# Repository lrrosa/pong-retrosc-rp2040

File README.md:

# RetroSC Pong — Raspberry Pi Pico (RP2040)

Pong para 1 ou 2 jogadores em um Raspberry Pi Pico, com saída de **vídeo
composto** (NTSC 1-bit gerado por PIO) e **áudio PWM**. Foi feito para uma
máquina arcade do evento [**RetroSC**](https://retrosc.org/).

## Recursos

- Vídeo composto NTSC 256×192, 1-bit, ~60 Hz, gerado inteiramente em PIO + DMA
  (CPU livre para o jogo).
- 2 raquetes controladas por **potenciômetros 10 kΩ** (ADC do Pico).
- **Dois modos**, escolhidos no menu do attract: **arcade** (1 jogador contra a
  CPU) e **versus** (2 jogadores). Os dois jogam as mesmas fases.
- **10 fases** em sequência, em ordem crescente de dificuldade, cada uma até
  9 pontos, e cada ponto soma no **total geral**:
  1. **PONG CLASSICO** — o pong de sempre;
  2. **TRIPLO** — a raquete vira 3 pedaços de 8 px com vãos entre eles;
  3. **NAVE** — uma nave sobe e desce no meio da quadra atirando: **a bola
     rebate nela** e o tiro que pega uma raquete deixa ela pela metade por 5 s;
  4. **BARREIRA I** — 2 muros de tijolos quebráveis no meio da tela;
  5. **PINBALL** — sete obstáculos fixos no meio da quadra: um losango com um
     poste solto acima e outro abaixo;
  6. **BARREIRA II** — 3 muros, agora espaçados entre si;
  7. **COLUNA** — cinco dos mesmos obstáculos, empilhados no meio e subindo e
     descendo juntos;
  8. **MURALHA** — uma parede de tijolos atrás de cada raquete: só marca ponto
     quem enfia a bola num dos vãos (a parede se refaz a cada ponto);
  9. **REBOUND** — vôlei: as raquetes deitam no chão e andam na horizontal
     dentro da própria meia-quadra, a bola tem gravidade e o ponto sai quando
     ela toca o chão do lado adversário;
  10. **BARREIRA III** — 4 muros (2 por jogador), já divididos em blocos de
      5-4-2-4-5 fileiras com um corredor vazio entre eles: a mais dura, por
      isso fecha o jogo.

  Nas três barreiras o estrago fica até o fim da fase: quando abre um vão de
  ponta a ponta, aquela fase volta a ser um pong normal.
- **Mascote-bônus**: em algumas fases (as que têm a quadra mais limpa) o
  mascote da RetroSC cruza a tela na diagonal — às vezes de cima para baixo,
  às vezes de baixo para cima — com a palavra **BONUS** piscando ao lado. Ele
  passa **no máximo duas vezes por fase**, e acertá-lo com a bola vale
  **3 pontos no total geral** de quem rebateu por último; o placar da fase não
  muda, e o total fica piscando um instante para o jogador perceber.
- **Pausa**: apertar o SELETOR durante a partida abre *CONTINUAR* / *SAIR DO
  JOGO*. A escolha anda pelo **movimento** do pot (não pela posição dele), então
  o menu sempre abre em *CONTINUAR*; o SELETOR confirma e sair volta ao attract.
  Passados **30 s**, a opção destacada vale sozinha — a tela não fica parada
  para sempre numa máquina de evento.
  Ao voltar ao jogo, a raquete de quem mexeu no pot durante a pausa fica
  **piscando e parada** até o pot voltar ao lugar em que estava — pausar não
  serve para reposicionar a raquete e salvar uma bola perdida.
- **Attract screen** com logo da RetroSC + demo automático (AI vs AI),
  revezando com a tabela de recordes a cada 20 s, e um **menu de modo** que só
  aparece depois de apertar o botão **SELETOR**.
- **High scores persistentes** na flash do RP2040 com **iniciais de 3 letras**
  estilo arcade — o pot escolhe cada letra e o botão SELETOR confirma. O que
  entra no ranking é o **total acumulado** (no arcade, sempre o do humano —
  ou seja, quanto ele fez até a fase em que parou).
- Áudio com os sons clássicos do Pong (raquete, parede, ponto) mais tijolo
  quebrado e beeps do menu, em PWM filtrado.
- Botão **SELETOR**: abre o menu, escolhe o modo e confirma as iniciais.

## Estrutura do repositório

```
pong-rp2040/
├── CMakeLists.txt
├── pico_sdk_import.cmake
├── README.md
├── LICENSE
├── docs/
│   ├── schematic.md     <-- esquemático por blocos (diagramas SVG)
│   ├── pinout.md        <-- pinagem dos 3 módulos RP2040 suportados
│   ├── bom.md           <-- lista de materiais (por referência: R1, C2, J4…)
│   ├── pecas-do-gabinete.md  <-- pots, knobs e itens da caixa: qual comprar
│   └── images/          <-- diagramas, renders da placa, capturas
├── kicad/               <-- PCB: 2 variantes, gerbers prontos p/ fábrica
│   ├── README.md        <-- pipeline (esquemático -> placa -> gerbers)
│   ├── retrosc-pong*.kicad_{sch,pcb,pro}
│   ├── retrosc-pong.pretty/   <-- footprints próprios (RCA, PAM8403)
│   └── gerbers*/ + *-gerbers.zip
├── src/
│   ├── main.c
│   ├── config.h         <-- constantes do projeto (pinos, dimensões, etc.)
│   ├── ntsc.{c,h,pio}   <-- driver de vídeo composto
│   ├── gfx.{c,h}        <-- desenho no framebuffer
│   ├── font.{c,h}       <-- fonte 5x7
│   ├── input.{c,h}      <-- ADC dos pots + botão
│   ├── audio.{c,h}      <-- PWM de áudio
│   ├── highscores.{c,h} <-- persistência na flash
│   ├── game.{c,h}       <-- máquina de estados, modos e física
│   ├── phases.{c,h}     <-- as 4 fases (raquetes especiais, tijolos)
│   └── assets.{c,h}     <-- bitmaps embutidos
└── tools/
    ├── png_to_c.py      <-- conversor PNG → C array
    ├── sim.py           <-- simulador do jogo (pygame)
    ├── crt_preview.py   <-- efeito de tubo nas capturas
    ├── gen_kicad_sch.py <-- gera o esquemático  (--yd p/ a variante)
    ├── gen_kicad_fp.py  <-- gera os footprints próprios
    ├── gen_kicad_pcb.py <-- gera a placa (placement, zonas, silk, logo)
    ├── make_decoy.py    <-- placa-isca p/ o Freerouting + DSN
    ├── import_ses.py    <-- traz o roteamento de volta
    └── dsn_tweak.py     <-- ajusta larguras/isolamento no DSN
```

## Hardware

Veja os arquivos em [docs/](docs/) para detalhes:

- [docs/schematic.md](docs/schematic.md) — esquemático completo
- [docs/pinout.md](docs/pinout.md) — pinagem dos **3 módulos RP2040
  suportados** (Pico oficial, YD-RP2040 de 3 botões e "roxa" de 1 botão) e
  qual variante de PCB usar com cada um
- [docs/bom.md](docs/bom.md) — lista de materiais e custo
- [docs/pecas-do-gabinete.md](docs/pecas-do-gabinete.md) — potenciômetros,
  manoplas e peças da caixa: **qual modelo comprar** e por quê
- [kicad/README.md](kicad/README.md) — as **duas variantes de PCB** prontas
  para fabricar (gerbers zipados)

Resumo do hardware:

| Bloco | GPIO | Componentes (referências do BOM) |
| ----- | ---- | -------------------------------- |
| Vídeo composto | GP16 (sync), GP17 (video) | R1 470 Ω + R2 270 Ω → jack J1 |
| Áudio | GP18 (PWM) | filtro R3 + C1, acoplamento C2, divisor R4/R5, entradas R6/R7 → amp U2 → jacks J8/J9 |
| Botão SELETOR | GP22 | SW1 (para GND) via header J7 |
| Potenciômetro P1 | GP26 (ADC0) | RV1 10 kΩ linear + C3 → header J5 |
| Potenciômetro P2 | GP27 (ADC1) | RV2 10 kΩ linear + C4 → header J6 |

Os GPIOs acima são os mesmos nos três módulos suportados; o que muda entre
eles é **em qual furo** cada GPIO aparece (ver [pinout.md](docs/pinout.md)).

## Como compilar

### 1. Instalar o Pico SDK

**Recomendado (Windows):** baixe o [Raspberry Pi Pico Windows Installer](https://github.com/raspberrypi/pico-setup-windows/releases),
que instala toolchain (ARM GCC), CMake, Ninja, Python e o Pico SDK de uma
vez.

**Manual (qualquer SO):**

```bash
git clone --depth 1 https://github.com/raspberrypi/pico-sdk.git
cd pico-sdk
git submodule update --init
export PICO_SDK_PATH=$(pwd)
```

Instale também:

- ARM GCC (`gcc-arm-none-eabi`)
- CMake ≥ 3.13
- Ninja ou Make

### 2. Build

```bash
git clone https://github.com/lrrosa/retrosc-pong.git
cd retrosc-pong
mkdir build && cd build
cmake -G "Ninja" ..   # ou simplesmente: cmake ..
ninja                 # ou: make -j
```

Resultado: `build/pong-rp2040.uf2`.

### 3. Gravar no Pico

1. Segure o botão **BOOTSEL** do Pico enquanto conecta o USB.
2. O Pico aparece como pendrive (`RPI-RP2`).
3. Arraste `pong-rp2040.uf2` para dentro do pendrive.
4. O Pico reinicia automaticamente rodando o jogo.

## Simulador (Python, sem hardware)

Para iterar em layouts e gameplay sem flashear o Pico, há um simulador que
roda a mesma lógica em Python e carrega os MESMOS bitmaps/fonte do código C:

```bash
pip install pygame
python tools/sim.py
```

Janela 768×576 (framebuffer 256×192 × 3). Controles:

- **Mouse Y na metade esquerda** → pot P1
- **Mouse Y na metade direita** → pot P2
- **Espaço** → botão SELETOR
- **N** → pula para a próxima fase (atalho de debug)
- `--fase N` na linha de comando → começa direto na fase N (0 a 9)
- **R** → zera high scores (só em RAM, não toca a flash do Pico)
- **Q** ou **ESC** → sair

Para regerar as capturas de tela usadas aqui (roda sem abrir janela):

```bash
python tools/sim.py --shots docs/images
python tools/crt_preview.py --all
```

Pré-visualizações com efeito CRT (como deve ficar numa TV de tubo —
scanlines, glow de fósforo, vignette e curvatura):

| Attract | Menu (só após o SELETOR) | Pausa |
| :---: | :---: | :---: |
|  |  |  |

As dez fases:

| 1 · pong clássico (com o mascote-bônus) | 2 · triplo | 3 · nave |
| :---: | :---: | :---: |
|  |  |  |

| 4 · barreira I | 5 · pinball | 6 · barreira II |
| :---: | :---: | :---: |
|  |  |  |

| 7 · coluna | 8 · muralha | 9 · rebound (vôlei) |
| :---: | :---: | :---: |
|  |  |  |

| 10 · barreira III | Fim de fase | Início de fase |
| :---: | :---: | :---: |
|  |  |  |

| Game Over | Enter Initials | High Scores |
| :---: | :---: | :---: |
|  |  |  |

Renderizações "raw" (sem CRT, só o framebuffer escalado) ficam em
`docs/images/sim_*.png`.

> **Limitação:** o simulador não reproduz a fidelidade do sinal NTSC nem
> o timing exato do PIO/DMA. Use para validar UX e visual; o teste final
> do vídeo só com a TV real.

### CRT preview

Para aplicar o efeito CRT (scanlines + bloom + fósforo + vignette +
curvatura) em qualquer PNG do framebuffer:

```bash
pip install pillow numpy
python tools/crt_preview.py docs/images/sim_attract.png        # gera crt_sim_attract.png
python tools/crt_preview.py --all                              # regenera todos os crt_*.png
```

Os parâmetros (intensidade do bloom, dos scanlines, cor do fósforo) estão
no topo de `crt_effect()` em [tools/crt_preview.py](tools/crt_preview.py)
e são bons pontos de partida; mexa neles pra ajustar pra TV verde, âmbar,
ou ajustar o "estado" do tubo.

## Simulador Wokwi (TV de verdade no navegador)

Diferente do simulador Python (que reproduz a lógica do jogo), o **Wokwi roda
o firmware compilado de verdade** no RP2040 emulado e mostra a saída de vídeo
composto numa **TV virtual** (`wokwi-tv`), com potenciômetros, botão e buzzer.

O `wokwi-tv` não usa DAC resistivo: ele lê os 2 pinos digitais direto e segue
os pulsos de sync (funciona com NTSC e PAL). Os arquivos já estão no repo:

- [`diagram.json`](diagram.json) — fiação: `GP16→SYNC`, `GP17→IN`, 2
  potenciômetros em `GP26`/`GP27`, botão SELETOR em `GP22`, buzzer em `GP18`.
- [`wokwi.toml`](wokwi.toml) — aponta para `build/pong-rp2040.uf2`/`.elf`.

Como rodar (extensão do VS Code, mais confiável que o site):

```bash
# 1. Compile o firmware
mkdir build && cd build && cmake -G Ninja .. && ninja && cd ..
# 2. No VS Code: instale a extensão "Wokwi for VS Code" e faça login (grátis)
# 3. Abra diagram.json e rode o comando "Wokwi: Start Simulator"
```

Controles no Wokwi: gire os **potenciômetros** (mouse) para mover as raquetes;
**botão verde** = SELETOR.

> **Importante:** abra a pasta `pong-rp2040` como raiz do workspace do VS Code
> (o `wokwi.toml` precisa estar na raiz). Se clicar em "play" e nada acontecer,
> rode antes `Ctrl+Shift+P` → "Wokwi: Request a New License" (token gratuito).

> **Velocidade:** o Wokwi roda a ~30% do tempo real — é normal. Emular o vídeo
> composto ciclo-a-ciclo no navegador é pesado. O **hardware real roda a 60 fps**
> (PIO + DMA fazem o vídeo, a CPU fica livre).

> **Se o Wokwi não abre no seu navegador:** ele exige WebAssembly + isolamento
> cross-origin (`SharedArrayBuffer`); extensões ou políticas às vezes bloqueiam.
> Use a **extensão do VS Code** (roda local) ou teste numa aba anônima. Se nem
> os projetos públicos do Wokwi rodam aí, conserte isso antes — não é do nosso
> projeto.

> **Centralização Wokwi × TV real:** a "janela visível" do `wokwi-tv` é
> deslocada para cima, então `LINES_TOP_BLANK` (em `src/config.h`) está em **55**
> para centralizar no simulador. Numa **TV CRT real** o centro padrão fica em
> **~30–35** — reduza esse valor (ou use o controle de V-Position/V-Hold da TV).
> A posição horizontal sai do "back porch" em `src/ntsc.pio`.

## Como jogar

- **Liga**: conecte alimentação (USB ou fonte 5 V). Sem ninguém jogando, a
  tela reveza entre o attract e a tabela de recordes.
- **Sair do attract**: aperte o **SELETOR** (vale também na tela de recordes).
  Só então o menu aparece — no attract ele fica escondido, para a tela seguir
  sendo a vitrine do jogo.
- **Escolher o modo**: com o menu aberto, **gire qualquer um dos dois pots**
  para trocar entre *MODO ARCADE* (1 jogador × CPU) e *MODO VERSUS*
  (2 jogadores) e aperte o **SELETOR** para confirmar. Sem toque nenhum por
  15 s, volta ao attract.
- **Jogar**: rode os potenciômetros para mover as raquetes (esquerda = P1,
  direita = P2 ou CPU). São **10 fases em sequência**, cada uma até **9
  pontos**, e todo ponto também soma no **total geral**. Cada fase começa com
  a bola indo para o lado de quem perdeu a fase anterior.
- **Como a partida acaba**:
  - No **modo arcade** ela termina assim que a CPU fecha uma fase — enquanto
    o jogador vencer, ele avança para a próxima. O placar dele é o total do
    que fez até ali, e a tela final mostra até que fase chegou.
  - No **modo versus** jogam-se as 10 fases e ganha quem tiver o maior total —
    mas a partida encerra antes se um dos dois **não alcançar mais o outro nem
    ganhando tudo o que falta**. A conta usa os pontos ainda em disputa (9 por
    fase restante, mais 6 nas fases que têm o bônus); se a diferença for
    exatamente igual a isso a partida continua, porque ainda dá empate. A tela
    de fim de fase avisa com *VANTAGEM DECISIVA*.
- **Ritmo**: a contagem 3-2-1 aparece só no primeiro ponto de cada fase; entre
  os pontos seguintes é só um "GO" rápido. Apertar o SELETOR pula as telas de
  início e de fim de fase — e, **durante a partida**, abre a pausa.
- **Iniciais**: se o total entrar no top 5, o jogador insere 3 letras estilo
  arcade — girar o pot rola pelo alfabeto A–Z, apertar o SELETOR confirma a
  letra atual e passa para a próxima. A tela tem **30 s**: no fim da contagem
  vale o que já estiver digitado. No modo arcade quem entra no ranking é
  sempre o humano (P1), tenha vencido ou não.
- **High scores**: depois das iniciais (ou direto, se não entrou no top),
  a tabela aparece por 10 s antes de voltar ao attract.

## Customização

Tudo importante está em [`src/config.h`](src/config.h):

- `PHASE_WIN_SCORE` — pontos para vencer **uma fase** (padrão 9). É o botão
  de volume da duração da partida. Medido no simulador: um jogador que vence
  as 10 fases leva ~18 min no arcade (quem perde na terceira sai em ~5 min), e
  uma partida versus equilibrada, que vai até a décima fase, passa de 30 min —
  quando um dos dois abre vantagem decisiva ela acaba antes. Para uma fila de
  evento, **5 pontos por fase** corta isso quase pela metade sem mudar mais
  nada.
- `AI_PADDLE_SPEED`, `AI_ERROR_PX` — dificuldade da CPU no modo arcade
  (velocidade em px/frame e erro de mira sorteado a cada rebatida).
- `BALL_SPEED_*` — física da bola
- `PADDLE_W`, `PADDLE_H`, `BALL_SIZE` — visual
- `BRICK_W`, `BRICK_H`, `TRIPLE_SEG_H`, `TRIPLE_GAP` — geometria das fases
- `BONUS_*` — o mascote-bônus: velocidade, inclinação, faixa horizontal, o
  intervalo sorteado entre passagens (`BONUS_WAIT_MIN/RANGE`), quantas vezes
  ele passa por fase (`BONUS_PASSES_MAX`) e quanto vale (`BONUS_POINTS`)
- `NAVE_*`, `SHOT_*`, `SHRINK_FRAMES` — a nave da fase 3, seus tiros e quanto
  tempo a raquete atingida fica pela metade
- `INITIALS_TIMEOUT_S`, `PAUSE_TIMEOUT_S` — os 30 s que cada tela de espera
  aguarda antes de decidir sozinha
- `BUMPER_*`, `COL_*`, `BUMPER_SPIN_SHIFT` — os obstáculos do pinball e da
  coluna móvel, e o quanto cada rebote neles gira a bola (o que impede que ela
  entre em vaivém eterno entre dois postes)
- `PAUSE_POT_STEP`, `PADDLE_TAKEOVER_TOL` — quanto girar o pot para trocar o
  item da pausa e a folga para a raquete voltar a obedecer depois dela
- `GRAVITY_Q`, `VOLLEY_*`, `NET_TOP` — a física do Rebound (vôlei)
- `MENU_TIMEOUT_S` — tempo até o menu desistir e voltar ao attract
- Pinos GPIO

As fases em si estão em [`src/phases.c`](src/phases.c): o enum `phase_id_t`,
as tabelas de nome/dica e as funções `build_*()`. Uma fase pode mexer em
quatro coisas — o formato/orientação da raquete, os tijolos e sólidos da
quadra, o ponto de saque e as *flags* (`PF_GRAVITY`, `PF_FLOOR_SCORES`,
`PF_SIDE_WALLS`, `PF_PADDLE_HORIZ`, `PF_NO_CENTER_LINE`, `PF_TEM_BONUS`) que
dizem ao `game.c` como tratar as bordas e a física e se o mascote-bônus
aparece ali. Para acrescentar uma fase basta um
item no enum, um nome/dica nas tabelas e o que ela tem de especial — o resto
do jogo (pontuação, menu, telas) não muda.

Ideias ainda na fila estão anotadas no topo de `phases.c`.

Para trocar o logo do attract:

```bash
python tools/png_to_c.py docs/images/seu_logo.png retrosc_logo 0 0 threshold > tools/_logo.inc
# Substituir o array correspondente em src/assets.c
```

Modo `threshold` (corte fixo em 128) é melhor para arte com contornos
definidos (logos, ícones). Modo `dither` (Floyd-Steinberg) é melhor para
fotos com gradientes — mas em 60 Hz num CRT, o padrão de dithering pode
ficar tremido. Para o evento, prefira `threshold`.

Veja `docs/images/preview_logo_1bit.png` para saber como ficou a versão
1-bit.

## Limitações conhecidas

- **NTSC monocromático**: sem cor. Em TVs PAL-M brasileiras, a maioria
  aceita o sinal sem problema (mostra em preto e branco). Se sua TV não
  aceita, talvez precise de uma TV CRT com entrada AV "real" ou um
  conversor.
- **Timing do PIO** está calculado para `clk_sys = 125 MHz`. Se você
  alterar o clock, ajuste `clkdiv` em `src/ntsc.c` proporcionalmente.
- **Serigrafia da PCB**: as placas da v1 têm o botão serigrafado como
  **START** (a net no KiCad também se chama `START`). O firmware, os diagramas
  e as telas já o chamam de **SELETOR** — é o mesmo botão no GP22.
- **Tabela de high scores zera ao atualizar**: o formato ganhou o campo de
  modo (`HISCORE_VERSION 3`), então a tabela gravada por firmwares antigos é
  descartada na primeira execução.

## Créditos e referências

- A abordagem de gerar NTSC com duas PIOs (sync + dados) + DMA é inspirada
  no trabalho de [@brucland](https://github.com/brucland/RP2040/tree/main/PIO/NTSC_1_bit).
  Este projeto é uma implementação independente (não copia o código), mas a
  análise daquele repositório foi essencial para definir o timing.
- Pong original: Allan Alcorn, Atari (1972).
- Logo da RetroSC: cortesia do evento [RetroSC](https://retrosc.org/).

## Licença

Projeto com **licença dupla** (ver [`NOTICE`](NOTICE) para o detalhamento por
arquivo):

- **Software** (firmware em `src/`, ferramentas em `tools/`, build) —
  **[GPL-3.0-or-later](LICENSE)** (`SPDX-License-Identifier: GPL-3.0-or-later`).
- **Hardware** (esquemáticos: `kicad/`, `docs/schematic.md`, `docs/bom.md`,
  `docs/pinout.md`, diagramas SVG) — **[CERN-OHL-S-2.0](LICENSE-HARDWARE.txt)**
  (`SPDX-License-Identifier: CERN-OHL-S-2.0`), a variante *Strongly Reciprocal*
  da CERN Open Hardware Licence.

As duas são **recíprocas** (copyleft): trabalhos derivados devem manter a mesma
licença e disponibilizar as fontes correspondentes (código no caso do software,
arquivos de projeto no caso do hardware).

As **marcas e arte do evento RetroSC** (logo) permanecem propriedade do evento e
**não** estão cobertas por essas licenças — ver [`NOTICE`](NOTICE).

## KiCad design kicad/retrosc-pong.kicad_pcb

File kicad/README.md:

# PCB — RetroSC Pong

Placa de 2 camadas com plano de terra, gerada por scripts (reprodutível) e
roteada com o Freerouting. Hardware sob **CERN-OHL-S-2.0** (ver
[`../LICENSE-HARDWARE.txt`](../LICENSE-HARDWARE.txt)).

| Montada | Sem componentes (serigrafia à mostra) |
| :---: | :---: |
|  |  |

**80 × 66 mm**, imagens da variante oficial (a YD é idêntica por fora; muda só
o roteamento). O logo RetroSC fica **embaixo do Pico** — por isso aparece na
serigrafia e não no render 3D. Layout detalhado em [Estado](#estado).

> O **Pico é o único componente com modelo 3D** (os footprints próprios do RCA
> e do PAM8403 não têm) — e é justamente ele que cobre o logo. Por isso a
> segunda vista é renderizada **sem componentes**: é nela que se confere a
> serigrafia. As três saem do passo 8 do pipeline.

**Duas variantes**, escolhidas pelo módulo RP2040 que você tem (mesma
furação, pinagens diferentes — ver [../docs/pinout.md](../docs/pinout.md) e
as marcas GP17/GP18 no silk):

| Variante | Módulo | Arquivos |
| --- | --- | --- |
| oficial | Raspberry Pi Pico **ou** YD-RP2040 de **3 botões** (pinagem ≈ Pico) | `retrosc-pong.*`, `gerbers/`, `retrosc-pong-gerbers.zip` |
| YD | RP2040 **roxa de 1 botão** (USB-C, 16 MB) | `retrosc-pong-yd.*`, `gerbers-yd/`, `retrosc-pong-yd-gerbers.zip` |

> Atenção: existem clones parecidos com pinagens diferentes entre si. O que
> define a variante é a **pinagem**, não a cor/marca — na dúvida, confira a
> tabela completa em `docs/pinout.md` e as marcas GP17/GP18.

## Como fabricar (é só isto)

1. Escolha a variante pela tabela acima — **qual módulo RP2040 você tem**.
2. Baixe o ZIP correspondente (`retrosc-pong-gerbers.zip` ou
   `retrosc-pong-yd-gerbers.zip`) e envie **como está** para a fábrica
   (JLCPCB, PCBWay, Elecrow…).
3. Parâmetros: **2 camadas, 1,6 mm, HASL**, 80 × 66 mm. Os defaults de
   qualquer fábrica servem — não há nada exótico na placa.
4. Peças e montagem: [../docs/bom.md](../docs/bom.md).

Não é preciso instalar KiCad nem rodar nada. O pipeline abaixo só interessa
para **modificar** o projeto.

## Arquivos versionados

| Arquivo | O quê |
| --- | --- |
| `retrosc-pong[-yd].kicad_sch` / `.kicad_pro` | esquemático e projeto |
| `retrosc-pong[-yd].kicad_pcb` | **placa roteada** (DRC 0 erros) |
| `retrosc-pong.pretty/` | footprints próprios (RCA de painel, PAM8403 HW-012) |
| `fp-lib-table` | registra a lib de footprints do projeto |
| `gerbers[-yd]/` | Gerbers + furação (Excellon) prontos para fábrica |
| `retrosc-pong[-yd]-gerbers.zip` | os mesmos gerbers zipados — **baixe e envie direto à fábrica** |
| `../docs/retrosc-pong[-yd]-esquematico.pdf` | esquemático completo em 1 folha (para montar/conferir) |

Intermediários (`*-decoy.*`, `*.dsn`, `*.ses`, `*.net`) são **gitignored** —
regeráveis pelo pipeline abaixo.

## Pipeline (do zero à placa roteada) — só para modificar

Esta seção é para quem vai **alterar** a placa: tudo é gerado por script, então
não se edita o `.kicad_pcb` à mão — muda-se o gerador e roda-se o pipeline de
novo. Requer o **Python do KiCad** (`.../KiCad/10.0/bin/python.exe`, módulo `pcbnew`),
`kicad-cli` e o **Freerouting** instalado.

```sh
KPY="/c/Program Files/KiCad/10.0/bin/python.exe"
CLI="/c/Program Files/KiCad/10.0/bin/kicad-cli.exe"
FR="$LOCALAPPDATA/freerouting/freerouting.exe"

# 1. esquemático -> netlist  (roda no Python normal)
python tools/gen_kicad_sch.py
python tools/gen_kicad_fp.py
"$CLI" sch export netlist -o kicad/retrosc-pong.net kicad/retrosc-pong.kicad_sch

# 2. placa (placement, contorno, zonas, regras)   [Python do KiCad]
"$KPY" tools/gen_kicad_pcb.py

# 3. ISCA sem zonas + DSN                          [Python do KiCad]
"$KPY" tools/make_decoy.py

# 4. roteamento automatico  (caminhos relativos: sem espacos)
"$FR" -de kicad/retrosc-pong-decoy.dsn -do kicad/retrosc-pong-decoy.ses -mp 100 -da

# 5. importar SES na placa real + remover trilhas de GND  [Python do KiCad]
"$KPY" tools/import_ses.py

# 6. preencher o plano e validar
"$CLI" pcb drc --refill-zones --save-board --severity-error \
       --exit-code-violations kicad/retrosc-pong.kicad_pcb

# 7. gerbers + furacao + zip para a fabrica
"$CLI" pcb export gerbers --layers "F.Cu,B.Cu,F.SilkS,B.SilkS,F.Mask,B.Mask,Edge.Cuts" \
       --subtract-soldermask -o kicad/gerbers/ kicad/retrosc-pong.kicad_pcb
"$CLI" pcb export drill --format excellon --drill-origin absolute \
       --excellon-units mm --generate-map --map-format gerberx2 \
       -o kicad/gerbers/ kicad/retrosc-pong.kicad_pcb
powershell -c "Compress-Archive -Path kicad\gerbers\* -DestinationPath kicad\retrosc-pong-gerbers.zip -Force"

# 8. imagens do README (montada, sem componentes, isometrica)
"$KPY" tools/render_placa.py

# 9. esquemático em PDF/SVG (o que se usa para montar e conferir)
"$CLI" sch export pdf -o docs/retrosc-pong-esquematico.pdf kicad/retrosc-pong.kicad_sch
"$CLI" sch export svg --no-background-color -o docs/images/kicad/ kicad/retrosc-pong.kicad_sch
# 10. desenho de encaixe na caixa            [Python do KiCad]
"$KPY" tools/fit_caixa.py
```

**Variante YD-RP2040:** repita os passos com `--yd` nos scripts Python e o
sufixo `-yd` nos nomes de arquivo (`retrosc-pong-yd.*`, `gerbers-yd/`). Entre
os passos 3 e 4, afine a trilha de sinal para 0,25 mm (com 0,30 mm o net
SELETOR não fecha nessa variante) e peça **0,17 mm de isolamento** ao roteador
— pedindo os 0,15 do projeto ele entrega 0,1478 e o DRC reprova:

```sh
python tools/dsn_tweak.py kicad/retrosc-pong-yd-decoy.dsn 250 500 170
```

**Por que a isca (passo 3):** com as zonas presentes, o DSN as exporta como
*planes* que o Freerouting trata como obstáculo — ele vira quase mono-camada e
abandona os nets longos. Sem zonas, roteia livre nas 2 faces; o plano de GND
volta na placa real e absorve todo o GND (passo 5 remove as trilhas de GND
redundantes).

## Estado

- **Placa 80 × 66 mm**, dimensionada para a caixa **Patola PB-085/3**
  (85 × 73 × 32 mm; interno ~82 × 70). Pico à esquerda com o USB na borda de
  cima; PAM8403 no topo à direita, corpo na placa e pot de volume saindo pela
  mesma borda; os 3 RCAs na borda direita com o **barril protraindo ~10 mm**
  (atravessa a parede da caixa); headers de painel em **uma fileira** na borda
  de baixo, cada pino com a função na serigrafia.
- **Nada de trilha sob os parafusos:** cada furo leva uma **área de exclusão
  de raio 3,6 mm** (rule area nas 2 faces) que barra trilhas e vias — sem
  ela o roteador passava sinal a 2 mm do centro, ou seja, 0,4 mm da borda do
  furo, bem debaixo da cabeça do parafuso. O plano de GND continua entrando
  (encostar em GND é inofensivo). `make_decoy.py` **preserva** essas áreas ao
  montar a isca, senão o roteador não as enxergaria.
- **Furos de montagem: 2, a 58 mm entre centros**, na linha de centro da
  largura — H1 (40, 4) e H2 (40, 62). É a furação dos **bossos da tampa** da
  PB-085/3 (2 bossos com furo-guia ø2,5, a 58 mm, no centro do lado de
  85 mm). Em troca, o miolo das bordas de cima e de baixo (x 36,5..43,5)
  fica reservado — nenhum componente pode ocupá-lo.
- **J5 + J6 (pots)** ficam na mesma fileira com **uma posição vaga** entre
  eles: um único conector fêmea 1×7 (2,54 mm) serve os dois, deixando o
  contato do meio sem uso. Por isso o par é indivisível — e, como não cabia
  junto do J4 sem os rótulos se embaralharem, a ordem na borda de baixo é
  **J4 · J7 · (J5 J6)**: o SELETOR (serigrafado START na v1), que é independente, ficou à esquerda e o
  par dos pots à direita do furo de montagem.
- **Encaixe na caixa** (desenho em escala abaixo): folga de **1,0 mm** nas
  laterais e **2,0 mm** em cima/embaixo; os 2 furos caem exatamente sobre os
  bossos da tampa. Recortes necessários na parede: **3 RCAs à direita**
  (barril passa 8,3 mm da face externa), **pot do amp em cima** (11,6 mm) e
  **USB em cima** — este último *não* protrai: a face do conector fica 1,2 mm
  para dentro, então o recorte precisa deixar o plugue entrar.

  > O desenho sai de `tools/fit_caixa.py`, que lê a geometria da própria
  > placa — refaça-o a cada mudança de layout. **A altura** (26 mm internos)
  > não está no desenho: confira na peça real, principalmente o eixo do pot e
  > os barris dos RCAs, cuja altura depende de quanto o parafuso afasta a
  > placa dos bossos.
- **Logo RetroSC no silk da frente**, dentro do espaço do Pico (48,4 ×
  15,2 mm a 0,22 mm/pixel, entre as duas fileiras de pinos — fica visível
  antes da montagem ou com o Pico socketado). Gerado de
  `docs/images/logo_retrosc_1bit.png` com preto/branco invertidos (o traço
  do logo é a tinta). O logo é marca do evento e **não** é coberto pelas
  licenças do projeto.
- **Marcas GP17/GP18 no silk** ao lado dos furos correspondentes de cada
  variante (Pico: coluna direita, posições 22/24; YD-RP2040: cantos da base,
  posições 20/21). Antes de soldar, confira se elas batem com os rótulos do
  seu módulo — é o jeito rápido de ver se a placa e o módulo são da mesma
  variante.
- **Serigrafia:** rótulos de função por pino, nome + referência em cada
  header (ex.: `POT P1 (J5)`), marcas GP17/GP18 **com linha de chamada** até
  o pino exato, e os nomes dos RCAs **na vertical**, encostados em cada jack
  (assim acompanham a altura do conector e não invadem a faixa dos headers).
  No meio da placa fica a assinatura `RetroSC Pong v1.0` + `LRRosa 2026`. As referências que
  caíam sobre pads (J*, H*) foram ocultadas — a informação está nos rótulos
  descritivos. O logo foi reescalado (0,19 mm/px) para caber **entre** as
  duas linhas verticais do footprint do Pico.
- **DRC: 0 erros**, 0 silk sobre cobre e 0 sobreposições. Restam 12 avisos
  de `silk_edge_clearance`: são o desenho do USB e dos barris dos RCAs
  cruzando a borda — intencional, é por ali que eles saem da caixa.
- Regras: trilha de sinal 0,3 mm, isolamento 0,15 mm, via 0,7/0,35 mm (JLCPCB
  2 camadas).

## ATENÇÃO antes de fabricar

- **Footprints do RCA e do PAM8403 foram feitos à mão** a partir de medidas das
  peças. Confira o encaixe (imprima o **desenho de fabricação** em 1:1 e
  sobreponha as peças) antes de enviar para produção.
- Peças de **painel** (pots, botão, chave A/B) saem por headers (J4–J7); os RCAs
  e o amp ficam **na placa**, como no protótipo.

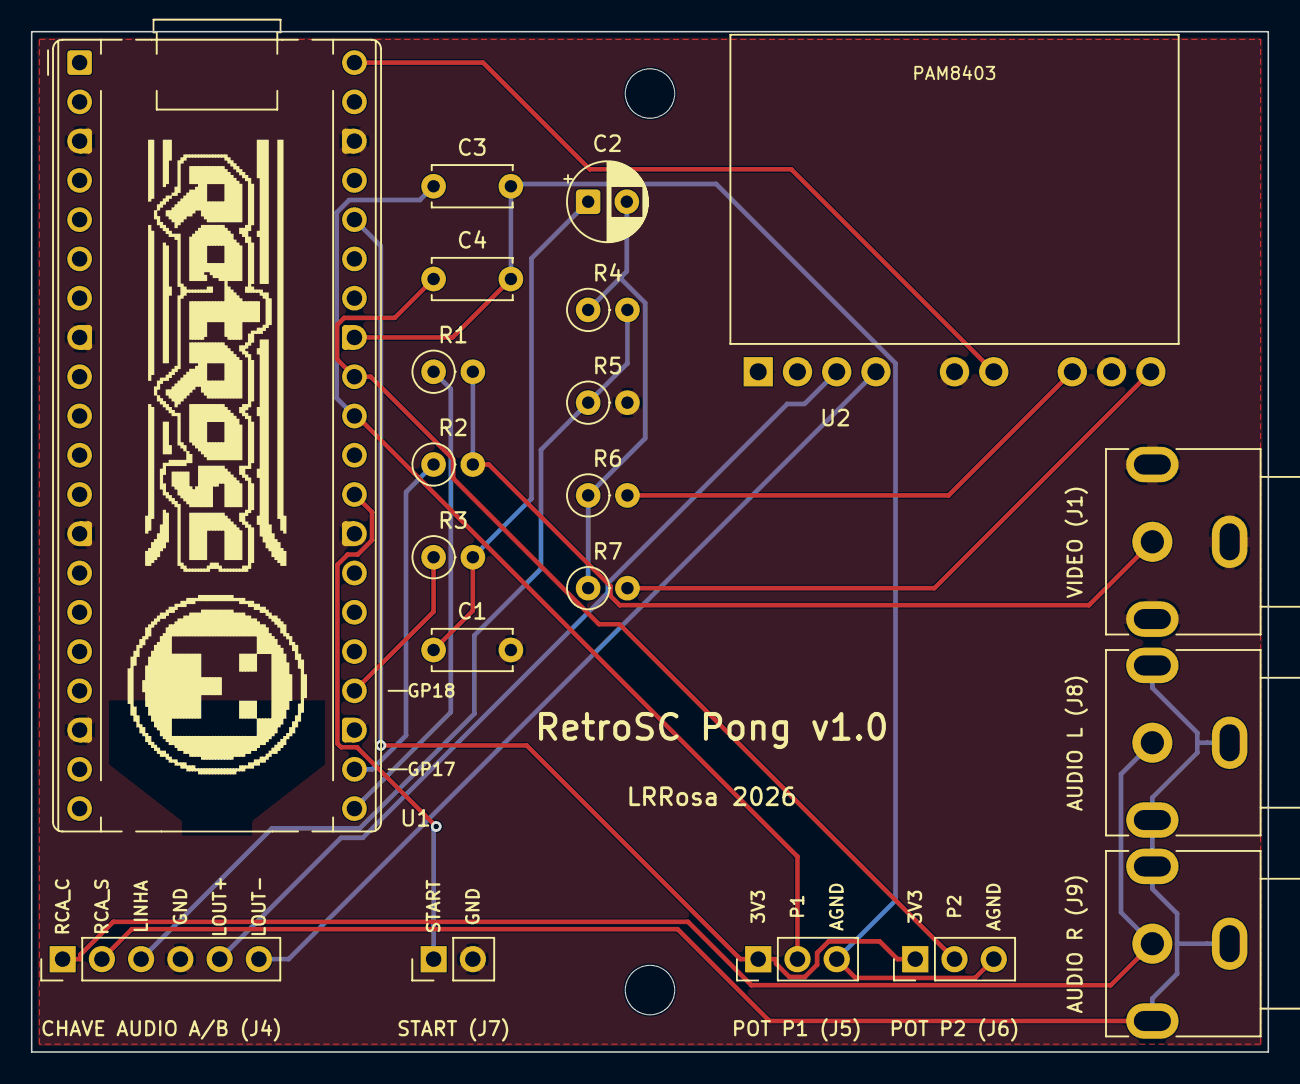
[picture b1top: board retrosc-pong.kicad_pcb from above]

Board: 2 copper layers, 80.0 x 66.0 mm, 22 parts (0 on the bottom side), 20 nets.

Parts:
C1, C3, C4: 100n; C_Disc_D5.0mm_W2.5mm_P5.00mm
C2: 1u; CP_Radial_D5.0mm_P2.50mm
H1, H2: MountingHole_3.2mm_M3
J1: RCA video (na placa); RCA_Jack_THT_Panel
J4: chave A/B (painel); PinHeader_1x06_P2.54mm_Vertical
J5: pot P1 (painel); PinHeader_1x03_P2.54mm_Vertical
J6: pot P2 (painel); PinHeader_1x03_P2.54mm_Vertical
J7: START (painel); PinHeader_1x02_P2.54mm_Vertical
J8: RCA audio L (na placa); RCA_Jack_THT_Panel
J9: RCA audio R (na placa); RCA_Jack_THT_Panel
R1: 470; R_Axial_DIN0207_L6.3mm_D2.5mm_P2.54mm_Vertical
R2: 270; R_Axial_DIN0207_L6.3mm_D2.5mm_P2.54mm_Vertical
R3, R5, R6, R7: 1k; R_Axial_DIN0207_L6.3mm_D2.5mm_P2.54mm_Vertical
R4: 10k; R_Axial_DIN0207_L6.3mm_D2.5mm_P2.54mm_Vertical
U1: RaspberryPi_Pico; RaspberryPi_Pico_Common_THT
U2: PAM8403 HW-012; PAM8403_HW-012

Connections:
+3V3: J5.1, J6.1, U1.36
+5V: U1.40, U2.6
AGND: C3.2, C4.2, J5.3, J6.3, U1.33
AMP_L: R6.2, U2.7
AMP_R: R7.2, U2.9
AUDIO_PWM: R3.1, U1.24
AUD_C: C2.2, R4.1, R6.1, R7.1
AUD_F: C1.1, C2.1, R3.2
COMPOSITE: J1.1, R1.2, R2.2
GND: C1.2, J1.2, J4.4, J7.2, R5.2, U1.3, U1.8, U1.13, U1.18, U1.23, U1.28, U1.38, U2.5, U2.8
LINHA: J4.3, R4.2, R5.1
LOUT_N: J4.6, U2.4
LOUT_P: J4.5, U2.3
POT1: C3.1, J5.2, U1.31
POT2: C4.1, J6.2, U1.32
RCA_C: J4.1, J8.1, J9.1
RCA_S: J4.2, J8.2, J9.2
START: J7.1, U1.29
SYNC: R1.1, U1.21
VIDEO: R2.1, U1.22

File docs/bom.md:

# Lista de Materiais (BOM)

Componentes para **uma unidade** do RetroSC Pong. As referências (R1, C2, J4…)
são as mesmas do esquemático, da serigrafia da placa e dos arquivos KiCad —
use-as para conferir cada peça no lugar certo.

> **Qual modelo comprar** de potenciômetro, manopla e demais peças da caixa
> (que duram num arcade, e por quê): [pecas-do-gabinete.md](pecas-do-gabinete.md).
> Aqui ficam as **quantidades e as referências**.

## 1. Componentes da placa

Tudo aqui vai **soldado na PCB** ([kicad/README.md](../kicad/README.md)).

| Ref | Qtd | Componente | Valor / especificação | Função |
| --- | --: | ---------- | --------------------- | ------ |
| R1 | 1 | Resistor 1/4 W | **470 Ω** | DAC de vídeo — sync |
| R2 | 1 | Resistor 1/4 W | **270 Ω** | DAC de vídeo — vídeo |
| R3 | 1 | Resistor 1/4 W | **1 kΩ** | filtro RC do áudio (com C1) |
| R4 | 1 | Resistor 1/4 W | **10 kΩ** | divisor de linha — série |
| R5 | 1 | Resistor 1/4 W | **1 kΩ** | divisor de linha — para GND |
| R6, R7 | 2 | Resistor 1/4 W | **1 kΩ** | entradas L e R do amplificador |
| C1 | 1 | Capacitor cerâmico | **100 nF** | filtro RC do áudio (com R3) |
| C2 | 1 | Capacitor **eletrolítico** | **1 µF** | acoplamento DC — **polarizado, + para o lado do GP18** |
| C3, C4 | 2 | Capacitor cerâmico | **100 nF** | filtro dos ADCs (um por potenciômetro) |
| U1 | 1 | Módulo RP2040 | Pico, YD de 3 botões ou "roxa" de 1 botão | **a variante da PCB depende do módulo** — ver [pinout.md](pinout.md) |
| U2 | 1 | Módulo amplificador | **PAM8403 (HW-012)**, 2×3 W, 5 V | com potenciômetro de volume embutido |
| J1 | 1 | Jack RCA fêmea | de painel, ângulo reto, THT | vídeo composto |
| J8, J9 | 2 | Jack RCA fêmea | de painel, ângulo reto, THT | áudio L e R |
| J4 | 1 | Barra de pinos 1×6 | passo 2,54 mm | chave de áudio A/B |
| J5, J6 | 2 | Barra de pinos 1×3 | passo 2,54 mm | potenciômetros P1 e P2 |
| J7 | 1 | Barra de pinos 1×2 | passo 2,54 mm | botão START |

> Somando por valor, para a compra: **4 × 1 kΩ** (R3, R5, R6, R7),
> **3 × 100 nF** (C1, C3, C4), 1 × 470 Ω, 1 × 270 Ω, 1 × 10 kΩ e 1 × 1 µF.
>
> **Os jacks RCA e o módulo do amp usam footprints feitos à mão** a partir de
> medidas das peças reais — confira o encaixe antes de mandar fabricar
> (imprima o **desenho de fabricação** em 1:1 e sobreponha as peças).

## 2. Peças de painel

Não vão na placa: ficam no gabinete e chegam à PCB por **fio**, nos headers
J4–J7. A função de cada pino está na serigrafia.

| Ref | Qtd | Componente | Especificação | Liga em |
| --- | --: | ---------- | ------------- | ------- |
| RV1, RV2 | 2 | Potenciômetro | **10 kΩ linear (tipo B), com batente** — [qual comprar](pecas-do-gabinete.md#potenciômetros--escolha-por-durabilidade) | J5 e J6 |
| SW1 | 1 | Botão push NA | momentâneo, 12 mm | J7 |
| SW2 | 1 | Chave **DPDT** ON-ON | 2 polos / 6 pinos (serve uma seletora de tensão) | J4 |
| — | 2 | Manopla (knob) | Ø ~32 mm × ~20 mm, furo 6 mm — [como escolher](pecas-do-gabinete.md#knobs--manoplas) | eixo dos pots |
| — | 1 | Alto-falante | 4–8 Ω, 3 W | plugado num RCA de áudio no modo B |

> A chave **SW2 seleciona o que sai pelos RCAs de áudio**: posição A = nível de
> linha para a TV; posição B = saídas do amplificador para caixa passiva. Ver
> [schematic.md](schematic.md#chave-ab--rcas-de-áudio-linha-p-tv-ou-saídas-do-amp)
> — inclusive os **cuidados obrigatórios** do modo B.

## 3. Montagem e cabos

| Qtd | Item | Especificação | Observação |
| --: | ---- | ------------- | ---------- |
| 1 | **PCB** | 2 camadas, 80 × 66 mm, HASL | envie o ZIP de gerbers da variante certa |
| 1 | **Caixa Patola PB-085/3** | 85 × 73 × 32 mm | a placa foi dimensionada para ela; furos H1/H2 caem nos bossos da tampa |
| 2 | Parafuso auto-atarraxante | ~ø2,9 × 6 mm | prende a placa nos bossos da tampa (furo-guia ø2,5) |
| 1 | Conector fêmea 1×6 | passo 2,54 mm | cabo da chave A/B (J4) |
| 1 | Conector fêmea 1×7 | passo 2,54 mm | **serve os dois pots de uma vez** (J5+J6, com o contato do meio vago) |
| 1 | Conector fêmea 1×2 | passo 2,54 mm | cabo do botão (J7) |
| 1 | Cabo USB | micro-USB (Pico) ou **USB-C** (clones) | alimentação e gravação |
| — | Fio AWG 24–26 flexível | | painel → headers |

> Sem PCB dá para montar tudo em placa universal de 2,54 mm, como foi o
> protótipo — a pinagem é a mesma.

## Substituições aceitáveis

- **Resistores DAC**: 220 Ω no lugar do 270 Ω também funciona (branco ~1,1 V,
  um pouco "quente" — o 270 Ω foi validado na TV real com imagem melhor).
  Evite 1 kΩ + 470 Ω: branco despenca para ~0,6 V (imagem escura).
- **Amplificador**: LM386 com 8 componentes externos, TDA2030, ou módulos
  prontos baseados em PAM8302/PAM8403.
- **Módulo RP2040 (U1)**: além do Pico oficial, o projeto tem placa para a
  YD-RP2040 de 3 botões e para a "roxa" de 1 botão. Outros clones funcionam se
  expuserem GP16–18, GP22, GP26 e GP27 — mas confira a **posição física** de
  cada um em [pinout.md](pinout.md): elas variam entre clones, e é isso que
  decide qual variante de PCB fabricar.

## Custo estimado (Brasil, 2026)

- RP2040 board: R$ 35–60
- Pots + manoplas: R$ 15
- Amp + alto-falante: R$ 25
- Resistores / capacitores / botão / RCA / headers: R$ 15
- PCB (5 un. em fábrica china, sem frete): ~R$ 10/un.
- **Total eletrônico: ~R$ 100–125** (sem TV e gabinete)

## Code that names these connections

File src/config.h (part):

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
// ===== Pinos =====
// Video composto: DAC resistivo de 2 bits.
//   SYNC_PIN  --[470 ohm]--+
//   VIDEO_PIN --[270 ohm]--+---- RCA center (composite out)
//                          +---- 75 ohm  ---- GND (terminacao da TV)
#define NTSC_SYNC_PIN     16
#define NTSC_VIDEO_PIN    17
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// ===== Video =====
#define FB_WIDTH          256
#define FB_HEIGHT         192
#define FB_STRIDE_WORDS   (FB_WIDTH / 32)   // 8 words por linha
#define FB_WORDS          (FB_STRIDE_WORDS * FB_HEIGHT)

#define LINES_PER_FRAME   262
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
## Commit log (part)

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2026-05-25 Initial commit: RetroSC Pong para RP2040
    Pong 2-jogadores com saida composta NTSC (PIO+DMA), controles por
    potenciometros 10K, audio PWM, attract screen com logo RetroSC, e
    high scores persistentes na flash.
    - Driver NTSC 256x192 1-bit, ~60Hz, 2 state machines + DMA encadeado
    - DAC resistivo 2-bit (470 ohm + 220 ohm)
    - ADC dos pots em GP26/GP27, audio PWM em GP18, botao START em GP22
2026-05-25 fix: include <stdio.h> em game.c para snprintf
    Build limpo sem warnings. UF2 de 85 KB compila com Pico SDK 1.5.1.
2026-05-26 feat: simulador Python (pygame) com previews
    tools/sim.py reproduz a logica de game.c em Python carregando os mesmos
    bitmaps de src/assets.c e a mesma fonte de src/font.c. Mouse Y nas duas
    metades da tela = pots, espaco = START.
    Adiciona docs/images/sim_*.png (attract, countdown, play, game_over,
    highscores) e secao no README documentando o uso.
    Util pra iterar UX/visuais sem precisar flashear o hardware.
2026-05-26 chore: ignore Python __pycache__
2026-05-26 feat: conversor com preview de TV CRT
    tools/crt_preview.py aplica:
    - Upscale 4x nearest-neighbor (pixels nitidos)
    - Phosphor tint P4 (branco-esverdeado)
    - Bloom aditivo nos pixels brancos
    - Scanlines (uma linha escura a cada scale px)
    - Aperture grille suave (gap vertical)
2026-05-26 feat: novo logo HD, RETRO PONG, iniciais 3-letras estilo arcade
    Attract screen:
    - Logo retroSC redesenhado, 220x68, mono alta resolucao
    - Titulo agora "RETRO PONG" (era "PONG")
    - Removida linha "RETROSC.ORG"
    - Raquetes da demo (AI) constrangidas a zona inferior pra nao colidir
    com texto
2026-05-26 art: novo logo 1-bit feito a mao no Photoshop
    Substitui o logo gerado por threshold automatico por uma versao 1-bit
    editada manualmente no Photoshop CS5 (220x69). Letras "retroSC" e
    mascote ficaram bem mais limpos: contornos definidos, sem ruido nas
    bordas, otimo contraste para CRT.
    Sim e CRT previews regenerados com o novo logo.
2026-05-29 docs: recomenda Sakae FCP22E (conductive plastic + stopper)
    - BOM ganha secao "Potenciometros - escolha por durabilidade" com
    tier 1 (Sakae FCP22E w/ stopper), tier 2 (Bourns / Vishay) e tier 3
    (hobby genericos).
    - schematic.md menciona o stopper e a furacao de painel 10,5mm.
    Para uso em arcade, conductive plastic e essencial (10^7 ciclos vs ~10^5
    de pots de carbono). O stopper evita zona morta de 40 graus no FCP22E.

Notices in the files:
src/config.h:
Copyright (C) 2026 RetroSC Pong contributors
